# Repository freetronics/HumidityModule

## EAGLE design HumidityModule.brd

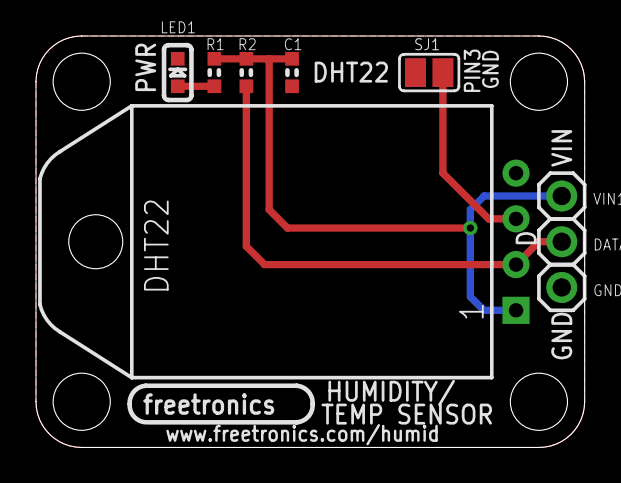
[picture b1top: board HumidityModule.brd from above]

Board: 2 copper layers, 30.5 x 22.9 mm, 9 parts (0 on the bottom side), 5 nets.

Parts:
C1: 100nF; 0603
DATA1: M01PTH; 1X01
GND1: M01PTH; 1X01
IC1: DHT22FLAT; DHT22
LED1: POWER; LED-0603
R1: 1K; 0603
R2: 10K; 0603
SJ1: SJ
VIN1: M01PTH; 1X01

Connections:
DATA: DATA1.1, IC1.2, R2.2
GND: C1.2, GND1.1, IC1.4, LED1.C, SJ1.1
unnamed: LED1.A, R1.1
unnamed: IC1.3, SJ1.2
VIN: C1.1, IC1.1, R1.2, R2.1, VIN1.1

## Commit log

2011-09-26 Initial project import
2011-09-28 Experimenting with dimensions. No good yet
2011-09-29 Added cap and routed board
2011-09-29 MoveD Da D
2011-09-29 Added cap value. Doh
2011-09-30 v1.0 released, also with pdf
2011-09-30 v1.1 release with VIN/DATA pad correction
2011-12-12 Schematic and Reference PDF renamed
2018-03-28 Improved designators

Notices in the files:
HumidityModule.brd:
(C)2011 Freetronics
